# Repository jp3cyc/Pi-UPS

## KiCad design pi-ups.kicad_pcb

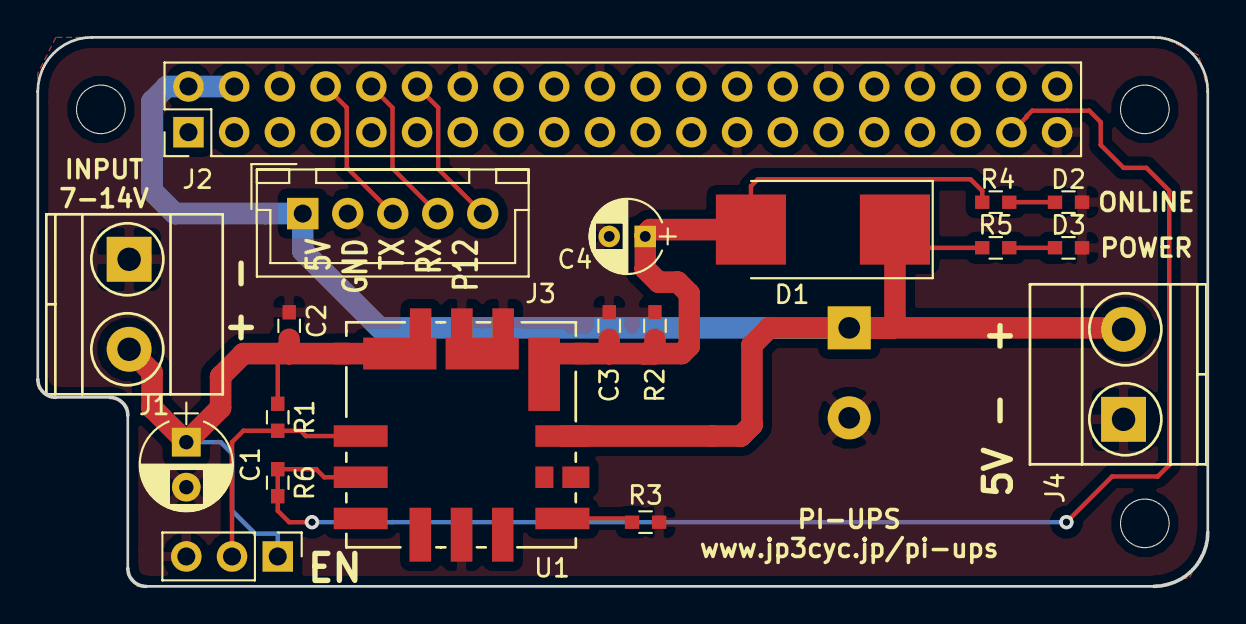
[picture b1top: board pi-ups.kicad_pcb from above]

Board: 2 copper layers, 65.0 x 30.5 mm, 20 parts (1 on the bottom side), 13 nets.

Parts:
C1: 22u; CP_Radial_D5.0mm_P2.50mm
C2, C3: 0.1u; C_0603
C4: 10u; CP_Radial_D4.0mm_P2.00mm
C5: SE-5R5-D155WY; CP_Radial_D14.0mm_P5.00mm
D1: D; D_3220
D2: ON-LINE; C_0603
D3: POWER; C_0603
J1: Battery; TerminalBlock_Pheonix_MKDS1.5-2pol
J2: Raspi GPIO; Pin_Header_Straight_2x20_Pitch2.54mm
J3: GPS; JST_XH_B05B-XH-A_05x2.50mm_Straight
J4: 5V; TerminalBlock_Pheonix_MKDS1.5-2pol
R1: 20k; C_0603
R2: 1.2k; C_0603
R3: 1.33k; C_0603
R4, R5: 1k; C_0603
R6: 0; C_0603
SW1: ON/OFF; Pin_Header_Straight_1x03_Pitch2.54mm
U1: OKL_T3_W12

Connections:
unnamed: C1.1, C2.2, J1.2, R1.1, SW1.1, U1.2
unnamed: C3.1, C4.1, D1.2, R2.1, R4.1, U1.4
unnamed: D2.2, R4.2
unnamed: D3.2, R5.2
unnamed: R1.2, SW1.2, U1.1
unnamed: R3.1, U1.6
pi-01: J2.1, J2.17
pi-02: C5.1, D1.1, J2.2, J2.4, J3.1, J4.2, R5.1, U1.5
pi-06: C1.2, C2.1, C3.2, C4.2, C5.2, D2.1, D3.1, J1.1, J2.6, J2.9, J2.14, J2.20, J2.25, J2.30, J2.34, J2.39, J3.2, J4.1, R2.2, R3.2, SW1.3, U1.3, U1.7
pi-08: J2.8, J3.3
pi-10: J2.10, J3.4
pi-12: J2.12, J3.5
pi-37: J2.37, R6.1, R6.2, U1.10

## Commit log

2019-03-10 add LICENSE
